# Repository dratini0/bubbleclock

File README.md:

# LED bubble display

This project is an ESP8266-based multiplexed driver for an 14 digit LED bubble display I have found somewhere.
It uses a separate battery charging and protection circuit, but has an internal LDO, more than capable enough to supply the display and the micro with sufficient power.

## Roadmap

- [x] Redesign with looser tolerances
- [x] Design and print case
- [x] Solder board
- [x] Finish MicroPython firmware, or develop native
  - [ ] Fix flickering issue

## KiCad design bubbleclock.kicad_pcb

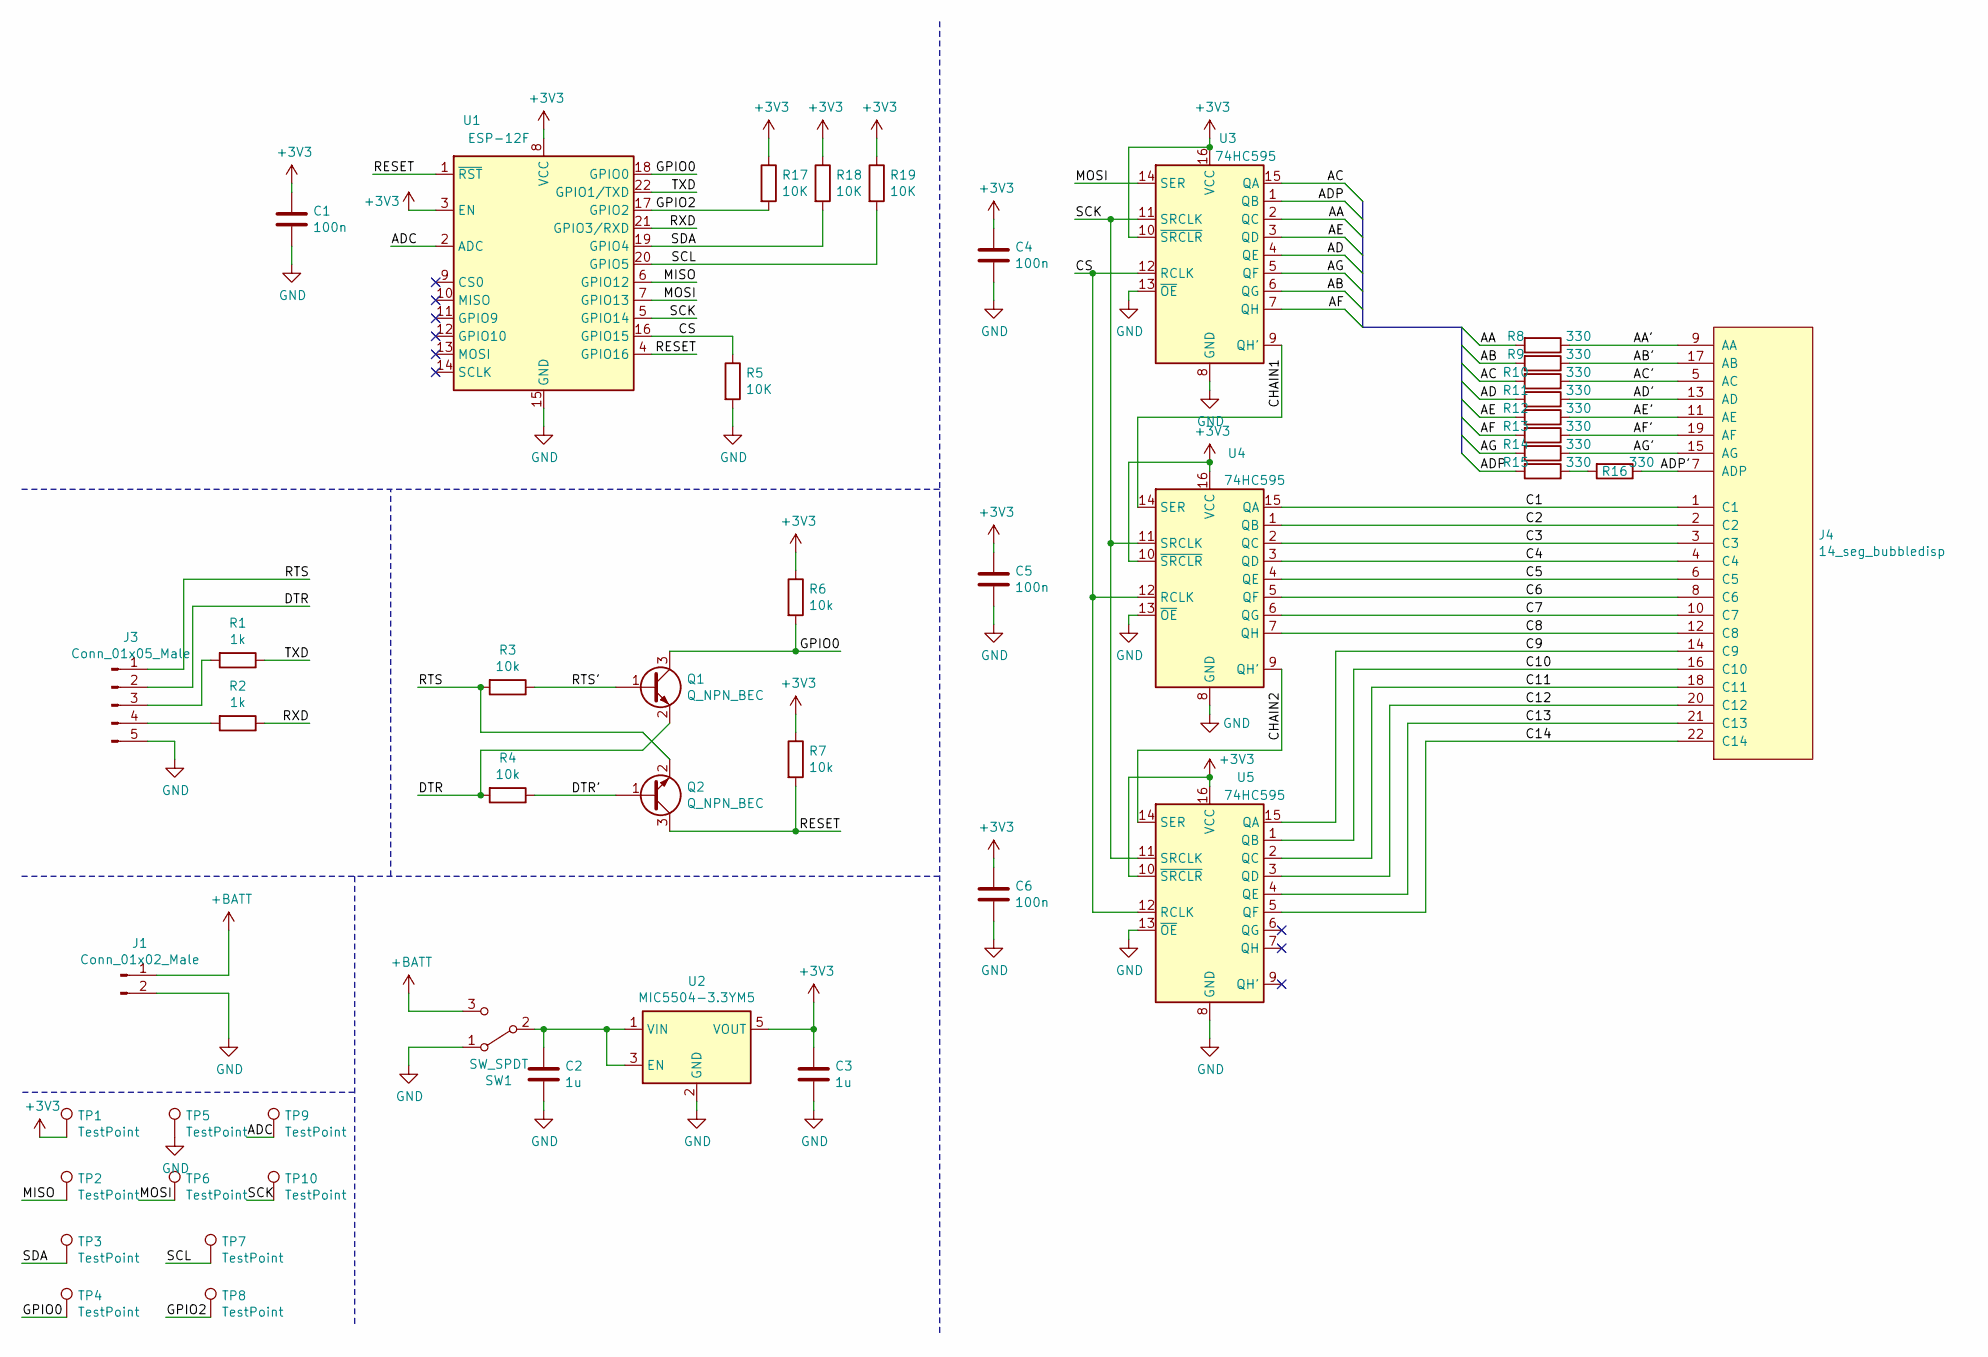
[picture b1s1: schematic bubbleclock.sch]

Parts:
C1, C4, C5, C6: 100n; C_0805_2012Metric_Pad1.15x1.40mm_HandSolder
C2, C3: 1u; C_0805_2012Metric_Pad1.15x1.40mm_HandSolder
J1: Conn_01x02_Male; PinHeader_1x02_P2.54mm_Vertical
J3: Conn_01x05_Male; PinHeader_1x05_P2.54mm_Horizontal
J4: 14_seg_bubbledisp; PinHeader_1x22_P2.54mm_Vertical
Q1, Q2: Q_NPN_BEC; SOT-23_Handsoldering
R1, R2: 1k; R_0805_2012Metric_Pad1.15x1.40mm_HandSolder
R3, R4, R6, R7: 10k; R_0805_2012Metric_Pad1.15x1.40mm_HandSolder
R5, R17, R18, R19: 10K; R_0805_2012Metric_Pad1.15x1.40mm_HandSolder
R8, R9, R10, R11, R12, R13, R14, R15, R16: 330; R_0805_2012Metric_Pad1.15x1.40mm_HandSolder
SW1: SW_SPDT; SW_SPDT_PCM12
TP1, TP2, TP3, TP4, TP5, TP6, TP7, TP8, TP9, TP10: TestPoint; TestPoint_Pad_2.5x2.5mm
U1: ESP-12F; ESP-12E
U2: MIC5504-3.3YM5; SOT-23-5_HandSoldering
U3, U4, U5: 74HC595; SOIC-16_3.9x9.9mm_P1.27mm

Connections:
+3V3: C1.1, C3.1, C4.1, C5.1, C6.1, R6.1, R7.1, R17.1, R18.1, R19.1, TP1.1, U1.3 (EN), U1.8 (VCC), U2.5 (VOUT), U3.10 (~SRCLR), U3.16 (VCC), U4.10 (~SRCLR), U4.16 (VCC), U5.10 (~SRCLR), U5.16 (VCC)
+BATT: J1.1, SW1.3 (C)
/AA: R8.2, U3.2 (QC)
/AA': J4.9 (AA), R8.1
/AB: R9.2, U3.6 (QG)
/AB': J4.17 (AB), R9.1
/AC: R10.2, U3.15 (QA)
/AC': J4.5 (AC), R10.1
/AD: R11.2, U3.4 (QE)
/AD': J4.13 (AD), R11.1
/ADC: TP9.1, U1.2 (ADC)
/ADP: R15.2, U3.1 (QB)
/ADP': J4.7 (ADP), R16.1
/AE: R12.2, U3.3 (QD)
/AE': J4.11 (AE), R12.1
/AF: R13.2, U3.7 (QH)
/AF': J4.19 (AF), R13.1
/AG: R14.2, U3.5 (QF)
/AG': J4.15 (AG), R14.1
/C1: J4.1 (C1), U4.15 (QA)
/C2: J4.2 (C2), U4.1 (QB)
/C3: J4.3 (C3), U4.2 (QC)
/C4: J4.4 (C4), U4.3 (QD)
/C5: J4.6 (C5), U4.4 (QE)
/C6: J4.8 (C6), U4.5 (QF)
/C7: J4.10 (C7), U4.6 (QG)
/C8: J4.12 (C8), U4.7 (QH)
/C9: J4.14 (C9), U5.15 (QA)
/C10: J4.16 (C10), U5.1 (QB)
/C11: J4.18 (C11), U5.2 (QC)
/C12: J4.20 (C12), U5.3 (QD)
/C13: J4.21 (C13), U5.4 (QE)
/C14: J4.22 (C14), U5.5 (QF)
/CHAIN1: U3.9 (QH'), U4.14 (SER)
/CHAIN2: U4.9 (QH'), U5.14 (SER)
/CS: R5.1, U1.16 (GPIO15), U3.12 (RCLK), U4.12 (RCLK), U5.12 (RCLK)
/DTR: J3.2, Q1.2 (E), R4.2
/DTR': Q2.1 (B), R4.1
/GPIO0: Q1.3 (C), R6.2, TP4.1, U1.18 (GPIO0)
/GPIO2: R17.2, TP8.1, U1.17 (GPIO2)
/MISO: TP2.1, U1.6 (GPIO12)
/MOSI: TP6.1, U1.7 (GPIO13), U3.14 (SER)
/RESET: Q2.3 (C), R7.2, U1.1 (~RST), U1.4 (GPIO16)
/RTS: J3.1, Q2.2 (E), R3.2
/RTS': Q1.1 (B), R3.1
/RXD: R2.1, U1.21 (GPIO3/RXD)
/SCK: TP10.1, U1.5 (GPIO14), U3.11 (SRCLK), U4.11 (SRCLK), U5.11 (SRCLK)
/SCL: R19.2, TP7.1, U1.20 (GPIO5)
/SDA: R18.2, TP3.1, U1.19 (GPIO4)
/TXD: R1.1, U1.22 (GPIO1/TXD)
GND: C1.2, C2.2, C3.2, C4.2, C5.2, C6.2, J1.2, J3.5, R5.2, SW1.1 (A), TP5.1, U1.15 (GND), U2.2 (GND), U3.8 (GND), U3.13 (~OE), U4.8 (GND), U4.13 (~OE), U5.8 (GND), U5.13 (~OE)
unnamed: C2.1, SW1.2 (B), U2.1 (VIN), U2.3 (EN)
unnamed: J3.3, R1.2
unnamed: J3.4, R2.2
unnamed: R15.1, R16.2

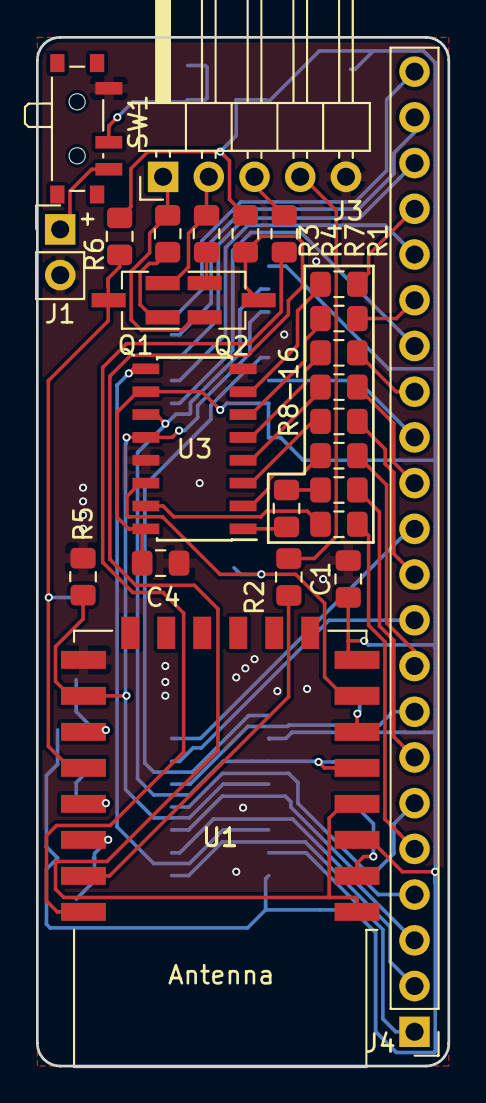
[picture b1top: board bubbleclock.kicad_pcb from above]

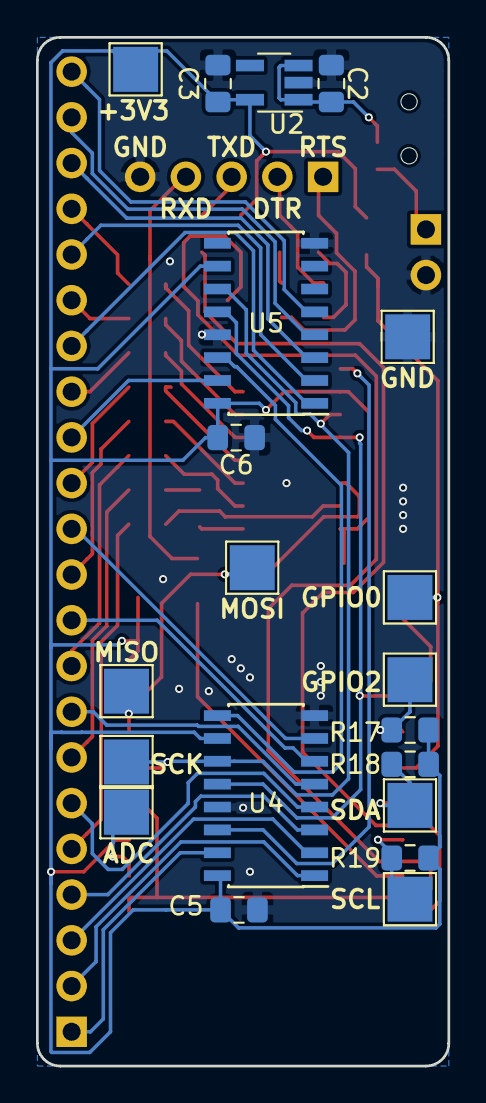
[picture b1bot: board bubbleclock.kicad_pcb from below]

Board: 2 copper layers, 22.9 x 57.2 mm, 46 parts (20 on the bottom side), 55 nets.

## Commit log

2018-12-14 Initial commit
    At this point, I have a board routed, but it is ugly and hard to get
    manufactured.
2018-12-14 schematic improvements. Board not updated, is broken.
    I pulled GPIO15 high instead of low. OOPS!
2018-12-15 Redesigned with looser tolerances
    Don't torture the boardhouse, plus implementing schematic fixes
    Fixes:
    1. Pull GPIO0 low instead of high
    2. Short regulator enable to VIN
2018-12-15 Set JLCPCB plotting prefs, move misplaced label
2018-12-19 Minimal tweaks, send to fab!
    * Move programming connector down
    * Add some sizes
2018-12-20 More messing with dimensions
2018-12-20 First layout of parts in case
2018-12-21 Draw the rest of the owl... case
2019-02-14 Add Gerbers and STL to .gitignore
2019-02-14 Change screw to M5x70
2019-02-15 improve tolerances
2019-02-15 Enlarge wiring compartment, remove BMS retention
2019-02-15 add a sample, separate meshess
    Ugh, wish we could export multiple meshes from openscad
2019-02-27 Fully round corners + note window size
    The bottom edges will get squashed, but it will still be smoother
2019-05-08 Ignore exported .stl files
2019-05-08 Add a test object
    (it turned out OK)
2019-05-08 Prototype software (too much flicker)
    I think the flicker is inherent from the RTOS on the ESP8266. So in the
    new design, we will add a 328p
2019-05-08 Move board designs to separate folder
2019-05-17 Update roadmap
